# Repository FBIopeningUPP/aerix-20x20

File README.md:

# **AERIX**

i wanted to design my own flight controller for fpv racing, so i made aerix. it fits a 20×20 mm stack and runs on an rp2354a with an icm-40609-d gyro.

i went with solder pads for the esc, receiver and vtx to keep the board small. the 8 rgb leds around the corners are there because they look cool af.

## front and back

| front | back |
| :---: | :---: |
|  |  |

## copper layers

<details>
<summary>see each layer up close</summary>

| front copper | inner copper 1 |
| :---: | :---: |
|  |  |

| inner copper 2 | back copper |
| :---: | :---: |
|  |  |

</details>

## files

- [kicad project](hardware/fc-v1/fc-v1.kicad_pro)
- [gerbers and drill files](hardware/production/fc-v1/fc-v1.zip)
- [interactive BOM](hardware/production/fc-v1/ibom.html) (download and open in a browser)

## bill of materials

| ref | part | qty |
| --- | --- | ---: |
| U1 | RP2354A microcontroller | 1 |
| U3 | ICM-40609-D gyro | 1 |
| U4 | W25Q128JVPIQTR flash | 1 |
| U5 | MP9943GQ-Z 5 V regulator | 1 |
| J1 | USB4105-GF-A USB-C port | 1 |
| LED10–LED17 | WS2812B-2020-V6 RGB LEDs | 8 |
| U2 | DPS368 barometer (optional) | 1 |

[full parts list with quantities and supplier links](hardware/production/fc-v1/aerix-bom.csv)

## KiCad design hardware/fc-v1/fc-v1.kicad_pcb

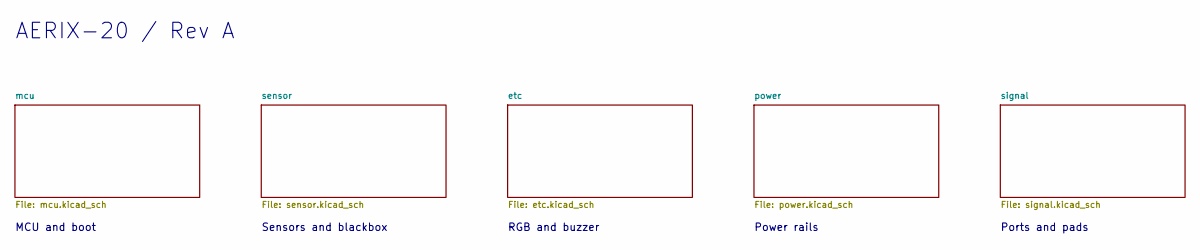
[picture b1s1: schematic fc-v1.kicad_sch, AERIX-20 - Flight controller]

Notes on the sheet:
Ports and pads
Sensors and blackbox
RGB and buzzer
AERIX-20 / Rev A
MCU and boot
Power rails

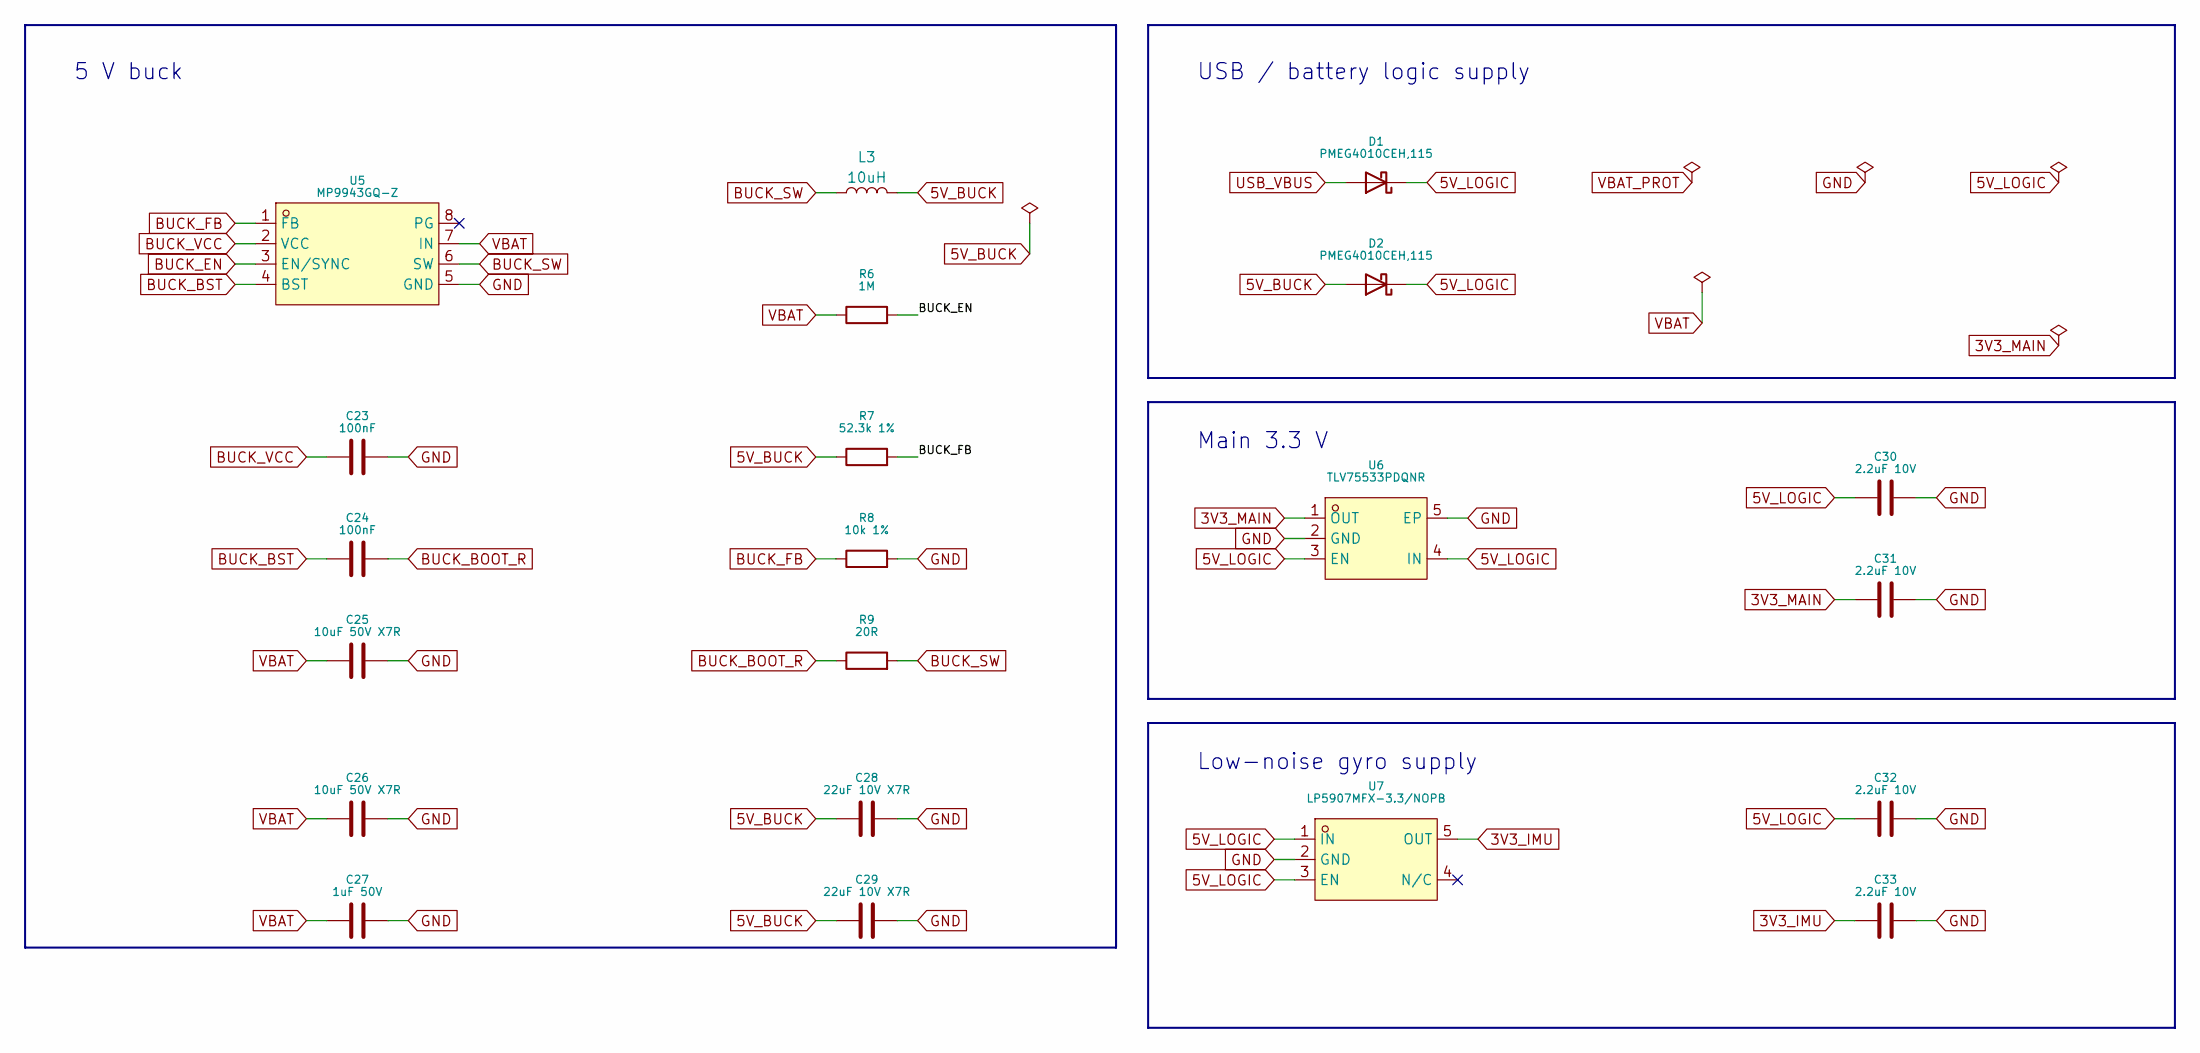
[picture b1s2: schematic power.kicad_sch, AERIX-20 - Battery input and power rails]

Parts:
C23, C24: 100nF; C_0402_1005Metric
C25, C26: 10uF 50V X7R; C_1210_3225Metric
C27: 1uF 50V; C_0603_1608Metric
C28, C29: 22uF 10V X7R; C_0805_2012Metric
C30, C31, C32, C33: 2.2uF 10V; C_0603_1608Metric
D1, D2: PMEG4010CEH,115; D_SOD-123F
L3: 10uH_1.0A_4018; L_APV_ANR4020; Part Number NRS4018T100MDGJ
R6: 1M; R_0402_1005Metric
R7: 52.3k 1%; R_0402_1005Metric
R8: 10k 1%; R_0402_1005Metric
R9: 20R; R_0402_1005Metric
U5: MP9943GQ-Z; QFN-8_L3.0-W3.0-P0.65-BL
U6: TLV75533PDQNR; X2SON-4_L1.0-W1.0-P0.65-TL-EP
U7: LP5907MFX-3.3/NOPB; SOT-23-5_L3.0-W1.7-P0.95-LS2.8-BR

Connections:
3V3_IMU: C33.1, U7.5 (OUT); also elsewhere on the board
3V3_MAIN: C31.1, U6.1 (OUT); also elsewhere on the board
5V_BUCK: C28.1, C29.1, D2.2 (A), L3.2, R7.1; also elsewhere on the board
5V_LOGIC: C30.1, C32.1, D1.1 (K), D2.1 (K), U6.3 (EN), U6.4 (IN), U7.1 (IN), U7.3 (EN)
BUCK_BOOT_R: C24.2, R9.1
BUCK_BST: C24.1, U5.4 (BST)
BUCK_EN: R6.2, U5.3 (EN/SYNC)
BUCK_FB: R7.2, R8.1, U5.1 (FB)
BUCK_SW: L3.1, R9.2, U5.6 (SW)
BUCK_VCC: C23.1, U5.2 (VCC)
GND: C23.2, C25.2, C26.2, C27.2, C28.2, C29.2, C30.2, C31.2, C32.2, C33.2, R8.2, U5.5 (GND), U6.2 (GND), U6.5 (EP), U7.2 (GND); also elsewhere on the board
USB_VBUS: D1.2 (A); also elsewhere on the board
VBAT: C25.1, C26.1, C27.1, R6.1, U5.7 (IN); also elsewhere on the board

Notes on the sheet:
5 V buck
USB / battery logic supply
Main 3.3 V
Low-noise gyro supply

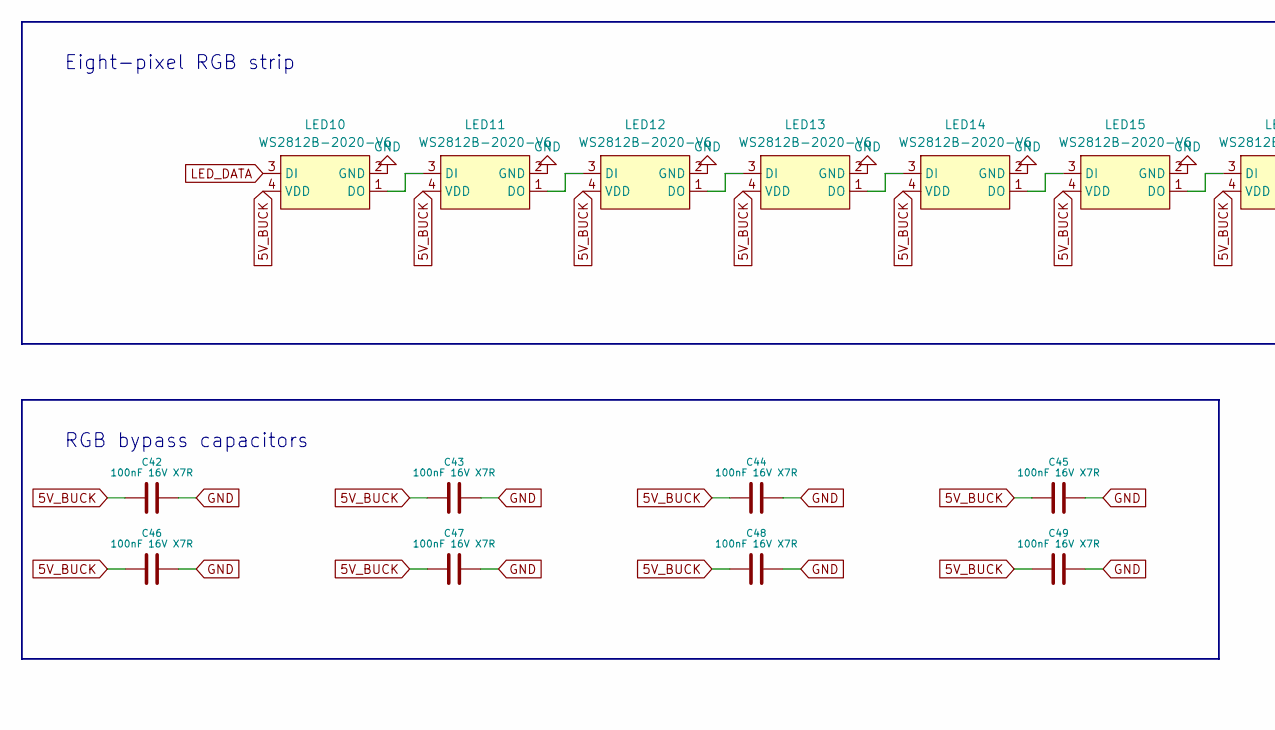
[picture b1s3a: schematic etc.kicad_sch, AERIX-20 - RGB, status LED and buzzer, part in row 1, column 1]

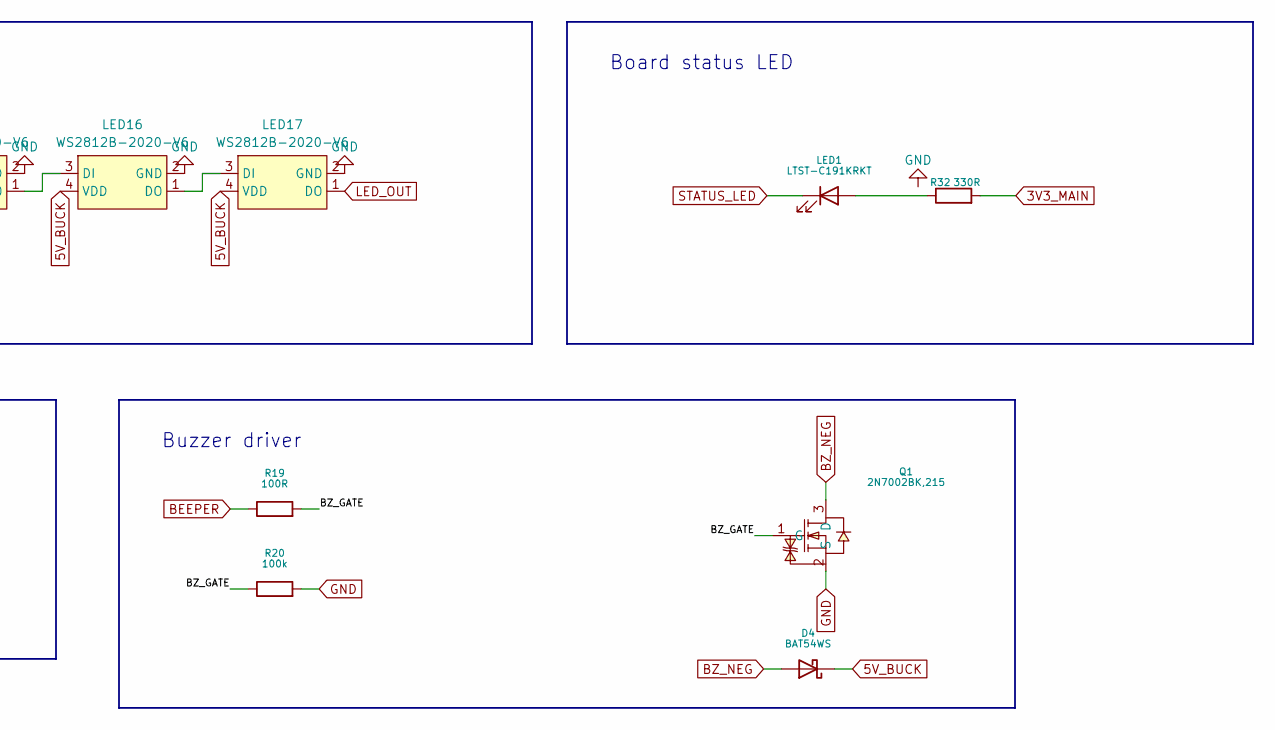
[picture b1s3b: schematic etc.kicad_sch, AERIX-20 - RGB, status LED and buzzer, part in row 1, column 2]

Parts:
C42, C43, C44, C45, C46, C47, C48, C49: 100nF 16V X7R; C_0402_1005Metric
D4: BAT54WS; D_SOD-323
LED1: LTST-C191KRKT; LED_0603_1608Metric
LED10, LED11, LED12, LED13, LED14, LED15, LED16, LED17: WS2812B-2020-V6; LED-SMD_4P-L2.2-W2.0-P1.00_WS2815C-2020-4P; MPN WS2812B-2020-V6; LCSC Part C52917434
Q1: 2N7002BK,215; SOT-23-3_L3.0-W1.7-P0.95-LS2.9-BR
R19: 100R; R_0402_1005Metric
R20: 100k; R_0402_1005Metric
R32: 330R; R_0402_1005Metric

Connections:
3V3_MAIN: R32.2; also elsewhere on the board
5V_BUCK: C42.1, C43.1, C44.1, C45.1, C46.1, C47.1, C48.1, C49.1, D4.1 (K), LED10.4 (VDD), LED11.4 (VDD), LED12.4 (VDD), LED13.4 (VDD), LED14.4 (VDD), LED15.4 (VDD), LED16.4 (VDD), LED17.4 (VDD); also elsewhere on the board
/etc/BZ_GATE: Q1.1 (G), R19.2, R20.1
BEEPER: R19.1; also elsewhere on the board
BZ_NEG: D4.2 (A), Q1.3 (D); also elsewhere on the board
GND: C42.2, C43.2, C44.2, C45.2, C46.2, C47.2, C48.2, C49.2, LED10.2 (GND), LED11.2 (GND), LED12.2 (GND), LED13.2 (GND), LED14.2 (GND), LED15.2 (GND), LED16.2 (GND), LED17.2 (GND), Q1.2 (S), R20.2; also elsewhere on the board
LED_DATA: LED10.3 (DI); also elsewhere on the board
LED_OUT: LED17.1 (DO); also elsewhere on the board
unnamed: LED1.2 (A), R32.1
unnamed: LED10.1 (DO), LED11.3 (DI)
unnamed: LED11.1 (DO), LED12.3 (DI)
unnamed: LED12.1 (DO), LED13.3 (DI)
unnamed: LED13.1 (DO), LED14.3 (DI)
unnamed: LED14.1 (DO), LED15.3 (DI)
unnamed: LED15.1 (DO), LED16.3 (DI)
unnamed: LED16.1 (DO), LED17.3 (DI)
STATUS_LED: LED1.1 (K); also elsewhere on the board

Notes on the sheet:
RGB bypass capacitors
Eight-pixel RGB strip
Board status LED
Buzzer driver

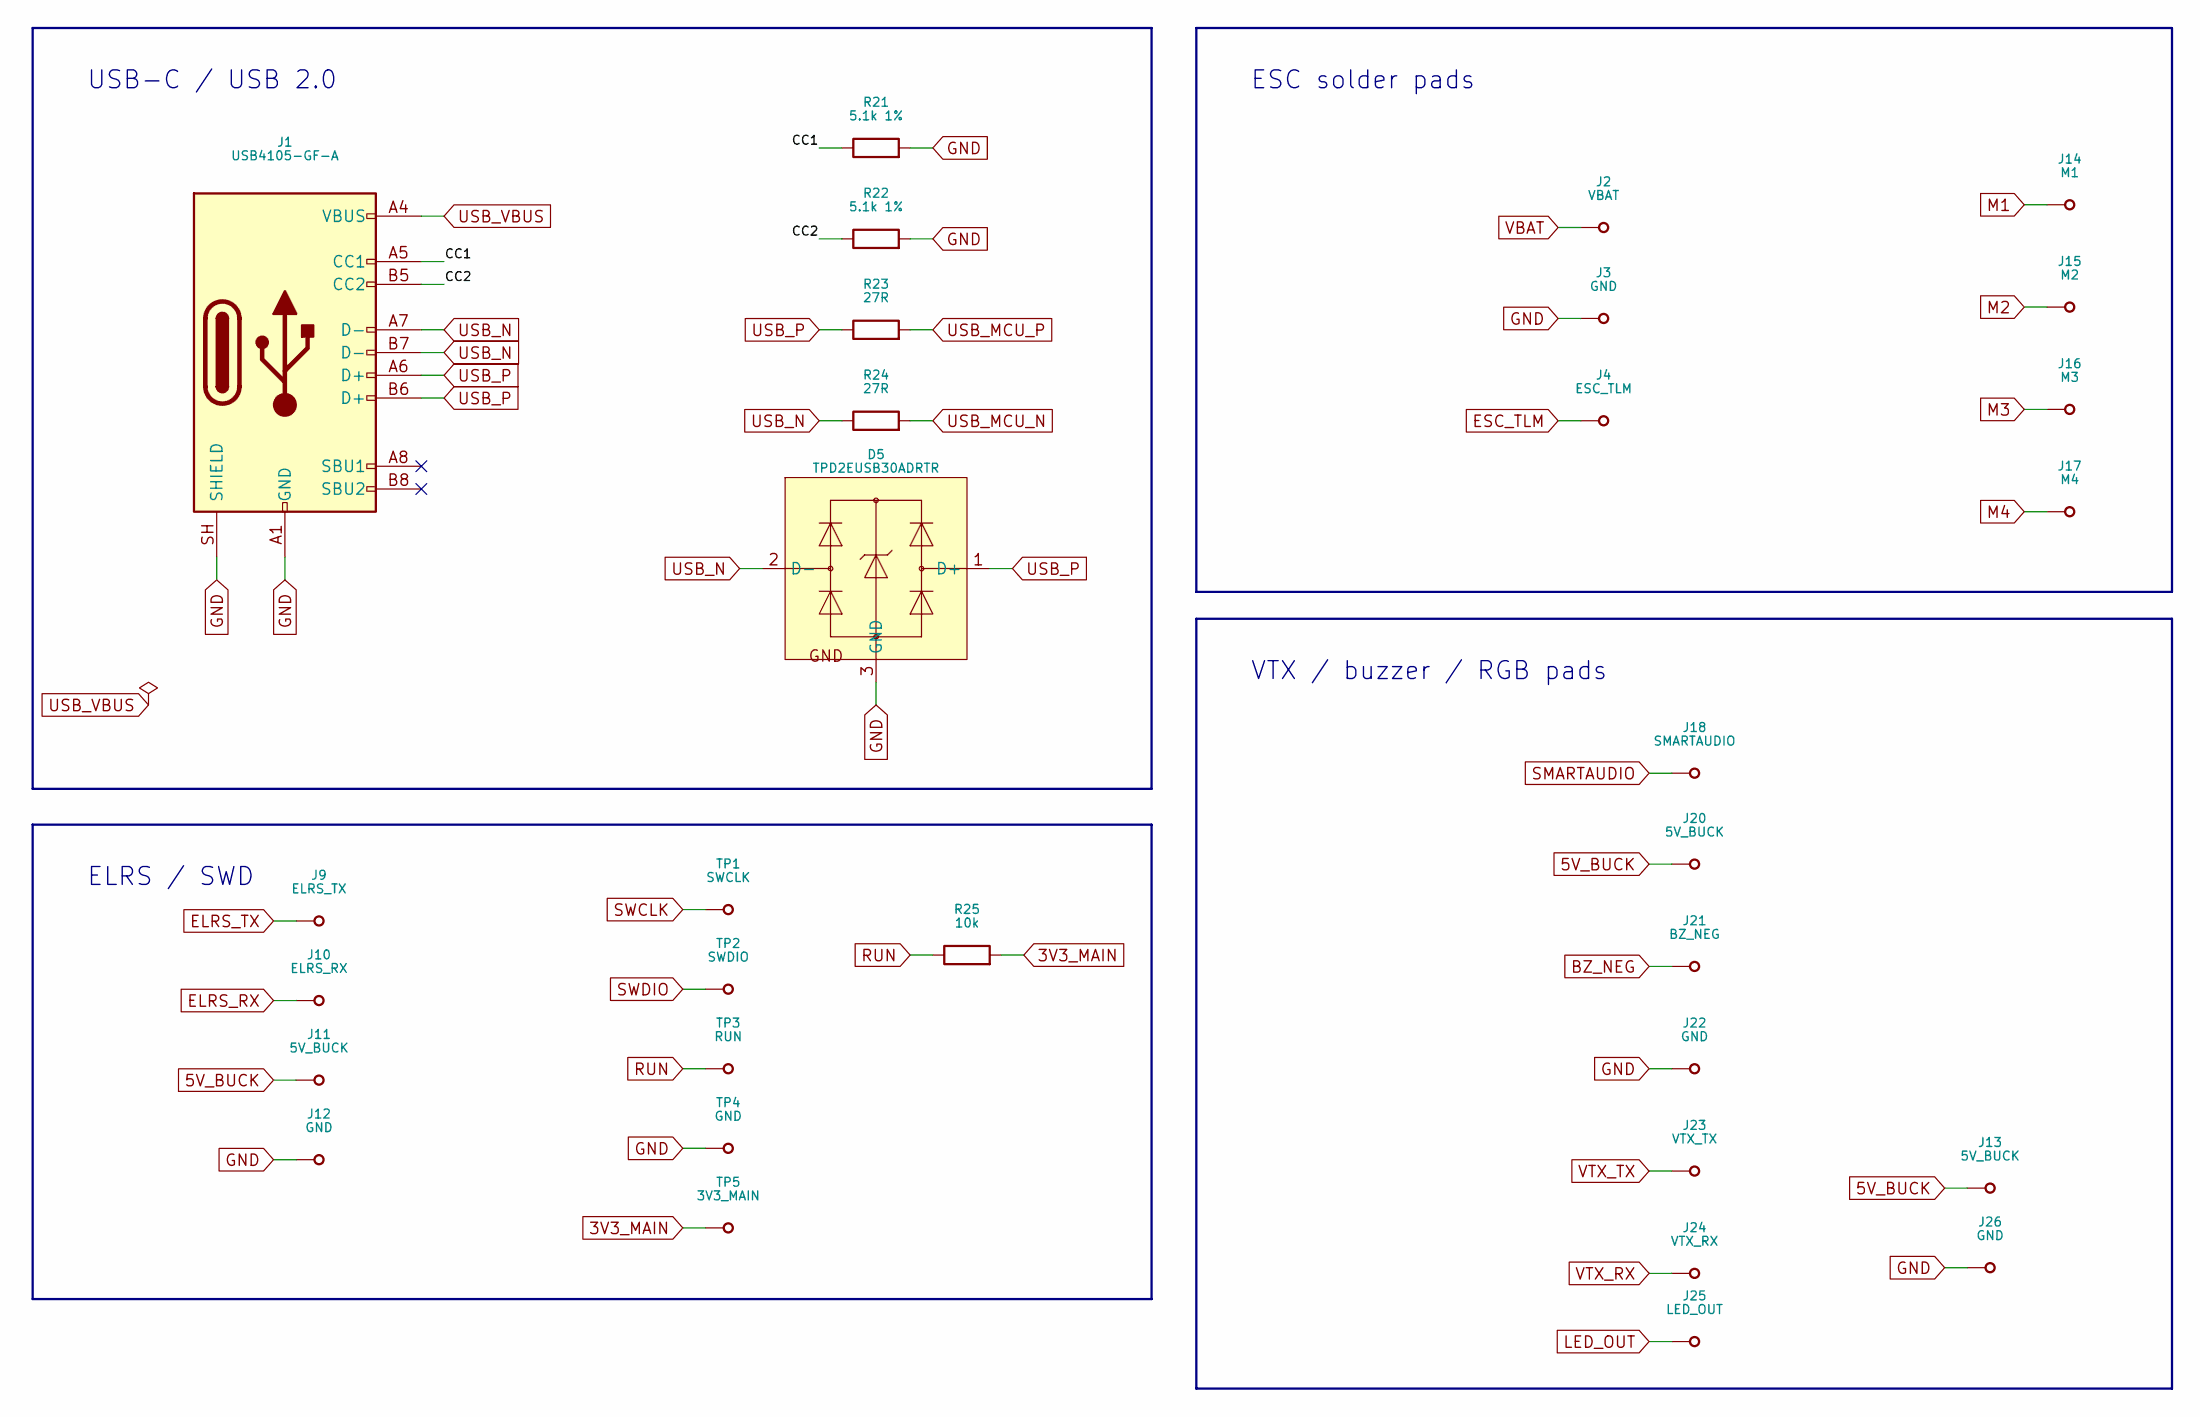
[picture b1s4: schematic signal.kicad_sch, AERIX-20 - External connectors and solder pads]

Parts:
D5: TPD2EUSB30ADRTR; SOT-9X3-3_L1.0-W0.8-P0.35-LS1.0-BR
J1: USB4105-GF-A; USB_C_Receptacle_GCT_USB4105-xx-A_16P_TopMnt_Horizontal
J2: VBAT; WirePad_2.0x2.5mm
J3: GND; WirePad_2.0x2.5mm
J4: ESC_TLM; WirePad_1.5x2.0mm
J9: ELRS_TX; WirePad_1.5x2.0mm
J10: ELRS_RX; WirePad_1.5x2.0mm
J11, J13, J20: 5V_BUCK; WirePad_1.5x2.0mm
J12, J22, J26: GND; WirePad_1.5x2.0mm
J14: M1; WirePad_1.5x2.0mm
J15: M2; WirePad_1.5x2.0mm
J16: M3; WirePad_1.5x2.0mm
J17: M4; WirePad_1.5x2.0mm
J18: SMARTAUDIO; WirePad_1.5x2.0mm
J21: BZ_NEG; WirePad_1.5x2.0mm
J23: VTX_TX; WirePad_1.5x2.0mm
J24: VTX_RX; WirePad_1.5x2.0mm
J25: LED_OUT; WirePad_1.5x2.0mm
R21, R22: 5.1k 1%; R_0402_1005Metric
R23, R24: 27R; R_0402_1005Metric
R25: 10k; R_0402_1005Metric
TP1: SWCLK; ProbePad_D1.0mm
TP2: SWDIO; ProbePad_D1.0mm
TP3: RUN; ProbePad_D1.0mm
TP4: GND; ProbePad_D1.0mm
TP5: 3V3_MAIN; ProbePad_D1.0mm

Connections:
3V3_MAIN: R25.2, TP5.1 (~_1); also elsewhere on the board
5V_BUCK: J11.1 (~_1), J13.1 (~_1), J20.1 (~_1); also elsewhere on the board
/signal/CC1: J1.A5 (CC1), R21.1
/signal/CC2: J1.B5 (CC2), R22.1
BZ_NEG: J21.1 (~_1); also elsewhere on the board
ELRS_RX: J10.1 (~_1); also elsewhere on the board
ELRS_TX: J9.1 (~_1); also elsewhere on the board
ESC_TLM: J4.1 (~_1); also elsewhere on the board
GND: D5.3 (GND), J1.A1 (GND), J1.A12 (GND), J1.B1 (GND), J1.B12 (GND), J1.SH (SHIELD), J3.1 (~_1), J12.1 (~_1), J22.1 (~_1), J26.1 (~_1), R21.2, R22.2, TP4.1 (~_1); also elsewhere on the board
LED_OUT: J25.1 (~_1); also elsewhere on the board
M1: J14.1 (~_1); also elsewhere on the board
M2: J15.1 (~_1); also elsewhere on the board
M3: J16.1 (~_1); also elsewhere on the board
M4: J17.1 (~_1); also elsewhere on the board
RUN: R25.1, TP3.1 (~_1); also elsewhere on the board
SMARTAUDIO: J18.1 (~_1); also elsewhere on the board
SWCLK: TP1.1 (~_1); also elsewhere on the board
SWDIO: TP2.1 (~_1); also elsewhere on the board
USB_MCU_N: R24.2; also elsewhere on the board
USB_MCU_P: R23.2; also elsewhere on the board
USB_N: D5.2 (D-), J1.A7 (D-), J1.B7 (D-), R24.1
USB_P: D5.1 (D+), J1.A6 (D+), J1.B6 (D+), R23.1
USB_VBUS: J1.A4 (VBUS), J1.A9 (VBUS), J1.B4 (VBUS), J1.B9 (VBUS); also elsewhere on the board
VBAT: J2.1 (~_1); also elsewhere on the board
VTX_RX: J24.1 (~_1); also elsewhere on the board
VTX_TX: J23.1 (~_1); also elsewhere on the board

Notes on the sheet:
VTX / buzzer / RGB pads
ESC solder pads
USB-C / USB 2.0
ELRS / SWD

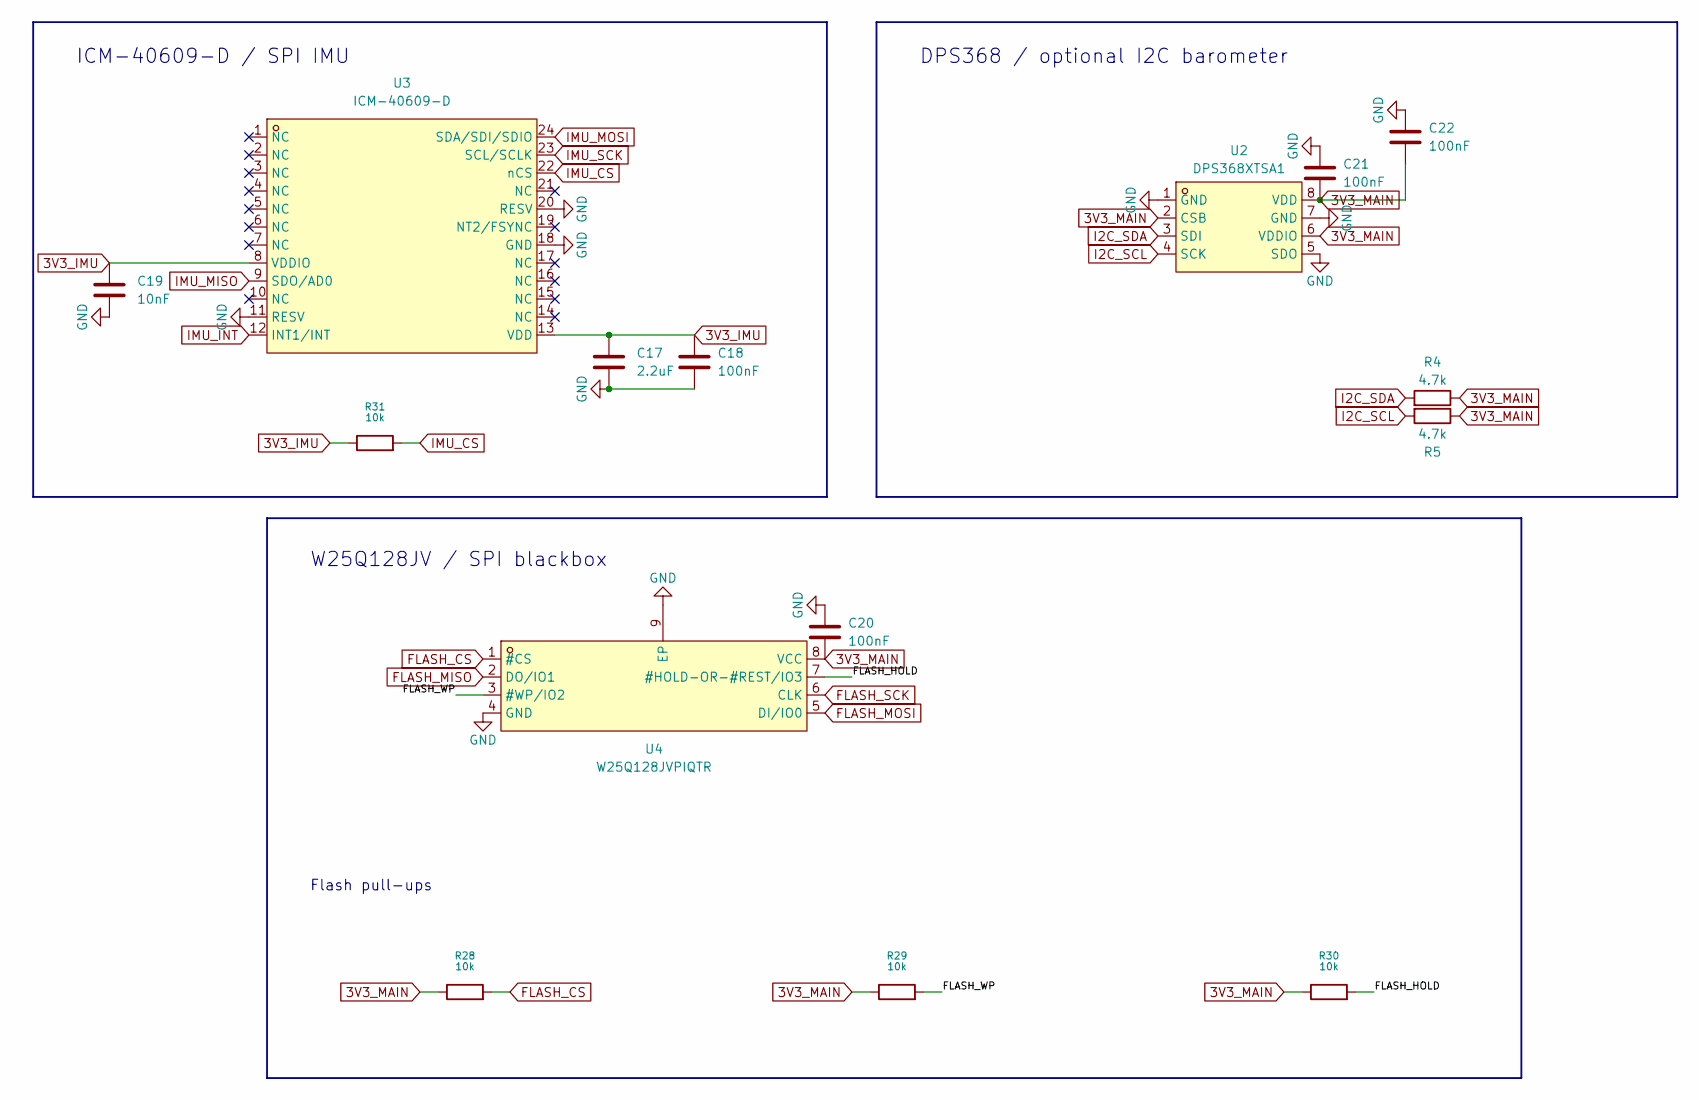
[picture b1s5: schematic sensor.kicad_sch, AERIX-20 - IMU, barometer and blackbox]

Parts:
C17: 2.2uF; C_0603_1608Metric
C18, C20, C21, C22: 100nF; C_0402_1005Metric
C19: 10nF; C_0402_1005Metric
R4, R5: 4.7k; R_0402_1005Metric
R28, R29, R30, R31: 10k; R_0402_1005Metric
U2: DPS368XTSA1; LGA-8_L2.5-W2.0-P0.65-TR_DPS368; MPN DPS368XTSA1; LCSC Part C3232508
U3: ICM-40609-D; LGA-24_L3.0-W3.0-P0.40-TL; MPN ICM-40609-D; LCSC Part C5360621
U4: W25Q128JVPIQTR; WSON-8_L6.0-W5.0-P1.27-BL-EP; MPN W25Q128JVPIQ; LCSC Part C190862

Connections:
3V3_IMU: C17.1, C18.1, C19.1, R31.1, U3.8 (VDDIO), U3.13 (VDD); also elsewhere on the board
3V3_MAIN: C20.2, C21.2, C22.2, R4.2, R5.2, R28.1, R29.1, R30.1, U2.2 (CSB), U2.6 (VDDIO), U2.8 (VDD), U4.8 (VCC); also elsewhere on the board
/sensor/FLASH_HOLD: R30.2, U4.7 (#HOLD-OR-#REST/IO3)
/sensor/FLASH_WP: R29.2, U4.3 (#WP/IO2)
FLASH_CS: R28.2, U4.1 (#CS); also elsewhere on the board
FLASH_MISO: U4.2 (DO/IO1); also elsewhere on the board
FLASH_MOSI: U4.5 (DI/IO0); also elsewhere on the board
FLASH_SCK: U4.6 (CLK); also elsewhere on the board
GND: C17.2, C18.2, C19.2, C20.1, C21.1, C22.1, U2.1 (GND), U2.5 (SDO), U2.7 (GND), U3.11 (RESV), U3.18 (GND), U3.20 (RESV), U4.4 (GND), U4.9 (EP); also elsewhere on the board
I2C_SCL: R5.1, U2.4 (SCK); also elsewhere on the board
I2C_SDA: R4.1, U2.3 (SDI); also elsewhere on the board
IMU_CS: R31.2, U3.22 (nCS); also elsewhere on the board
IMU_INT: U3.12 (INT1/INT); also elsewhere on the board
IMU_MISO: U3.9 (SDO/AD0); also elsewhere on the board
IMU_MOSI: U3.24 (SDA/SDI/SDIO); also elsewhere on the board
IMU_SCK: U3.23 (SCL/SCLK); also elsewhere on the board

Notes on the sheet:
ICM-40609-D / SPI IMU
DPS368 / optional I2C barometer
Flash pull-ups
W25Q128JV / SPI blackbox

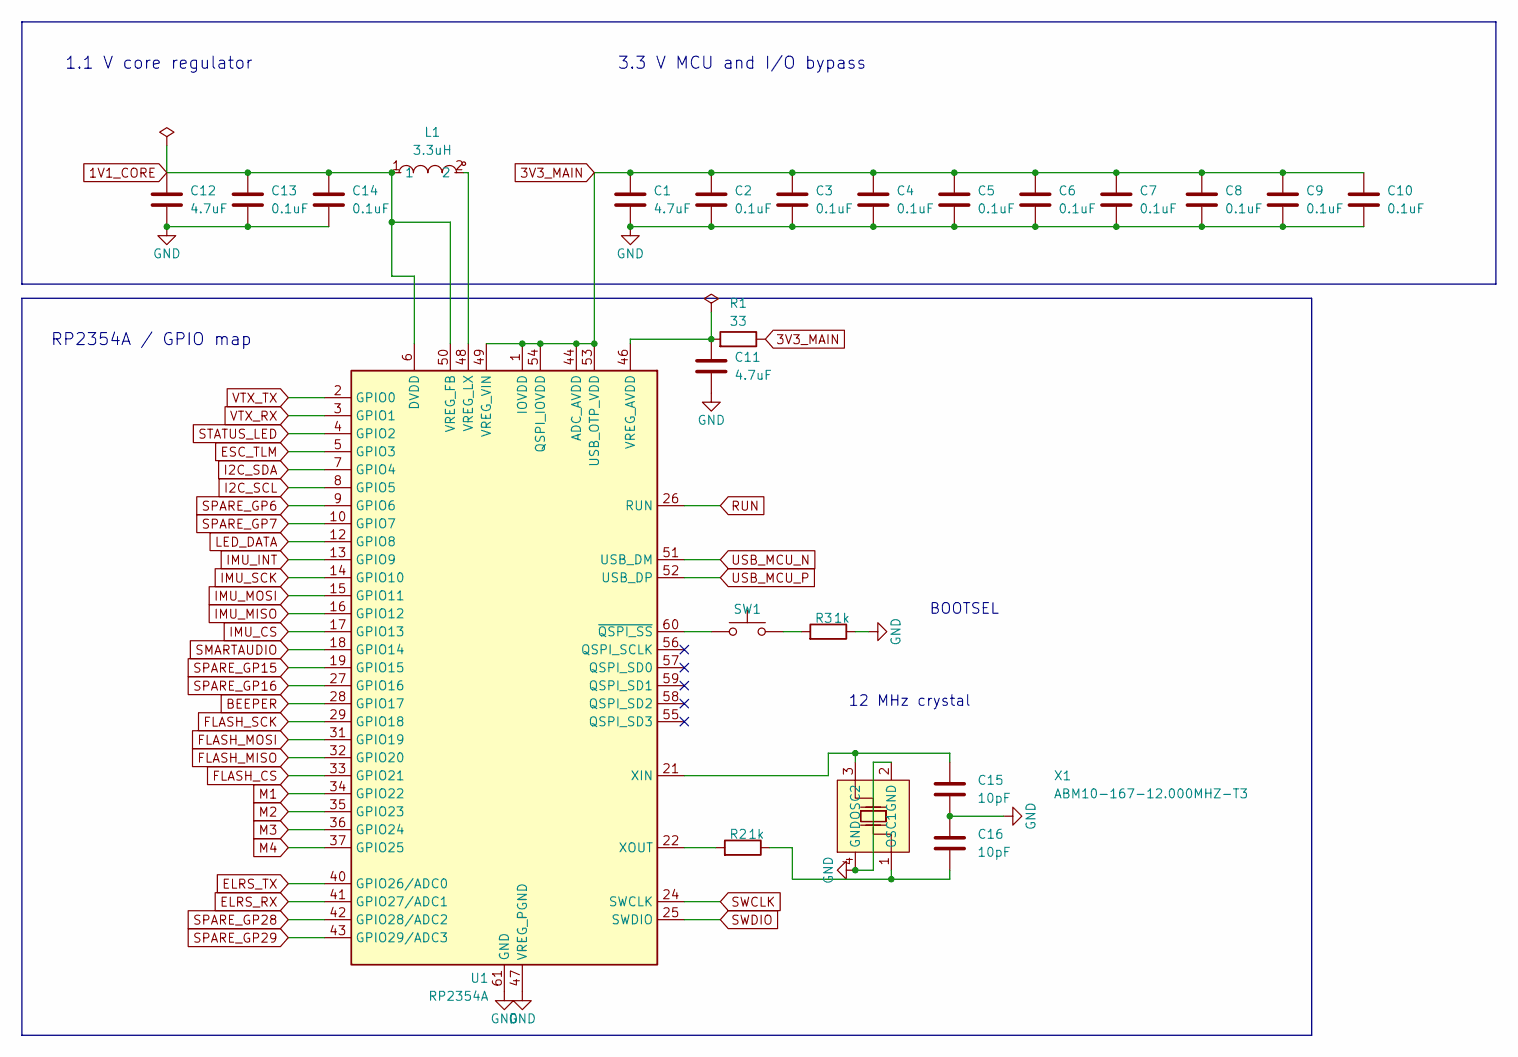
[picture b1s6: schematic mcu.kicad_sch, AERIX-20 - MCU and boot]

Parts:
C1, C11, C12: 4.7uF; C_0402_1005Metric
C2, C3, C4, C5, C6, C7, C8, C9, C10, C13, C14: 0.1uF; C_0402_1005Metric
C15, C16: 10pF; C_0402_1005Metric
L1: 3.3uH; IND-SMD_L2.0-W1.6_AOTA-B201610S3R3-101-T; MPN AOTA-B201610S3R3-101-T; LCSC Part C42411119
R1: 33; R_0402_1005Metric
R2, R3: 1k; R_0402_1005Metric
SW1: Momentary Tactile Button - Biege; Push_SMD_4.2x3.2mm_h2.5mm_Beige
U1: RP2354A; QFN-60-1EP_7x7mm_P0.4mm_EP3.4x3.4mm
X1: ABM10-167-12.000MHZ-T3; CRYSTAL-SMD_4P-L2.5-W2.0-BL; MPN ABM10-167-12.000MHZ-T3; LCSC Part C1985295

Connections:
1V1_CORE: C12.1, C13.1, C14.1, L1.1, U1.6 (DVDD), U1.23 (DVDD), U1.39 (DVDD), U1.50 (VREG_FB)
3V3_MAIN: C1.1, C2.1, C3.1, C4.1, C5.1, C6.1, C7.1, C8.1, C9.1, C10.1, R1.2, U1.1 (IOVDD), U1.11 (IOVDD), U1.20 (IOVDD), U1.30 (IOVDD), U1.38 (IOVDD), U1.44 (ADC_AVDD), U1.45 (IOVDD), U1.49 (VREG_VIN), U1.53 (USB_OTP_VDD), U1.54 (QSPI_IOVDD); also elsewhere on the board
BEEPER: U1.28 (GPIO17); also elsewhere on the board
ELRS_RX: U1.41 (GPIO27/ADC1); also elsewhere on the board
ELRS_TX: U1.40 (GPIO26/ADC0); also elsewhere on the board
ESC_TLM: U1.5 (GPIO3); also elsewhere on the board
FLASH_CS: U1.33 (GPIO21); also elsewhere on the board
FLASH_MISO: U1.32 (GPIO20); also elsewhere on the board
FLASH_MOSI: U1.31 (GPIO19); also elsewhere on the board
FLASH_SCK: U1.29 (GPIO18); also elsewhere on the board
GND: C1.2, C2.2, C3.2, C4.2, C5.2, C6.2, C7.2, C8.2, C9.2, C10.2, C11.2, C12.2, C13.2, C14.2, C15.2, C16.1, R3.2, U1.47 (VREG_PGND), U1.61 (GND), X1.2 (GND), X1.4 (GND); also elsewhere on the board
I2C_SCL: U1.8 (GPIO5); also elsewhere on the board
I2C_SDA: U1.7 (GPIO4); also elsewhere on the board
IMU_CS: U1.17 (GPIO13); also elsewhere on the board
IMU_INT: U1.13 (GPIO9); also elsewhere on the board
IMU_MISO: U1.16 (GPIO12); also elsewhere on the board
IMU_MOSI: U1.15 (GPIO11); also elsewhere on the board
IMU_SCK: U1.14 (GPIO10); also elsewhere on the board
LED_DATA: U1.12 (GPIO8); also elsewhere on the board
M1: U1.34 (GPIO22); also elsewhere on the board
M2: U1.35 (GPIO23); also elsewhere on the board
M3: U1.36 (GPIO24); also elsewhere on the board
M4: U1.37 (GPIO25); also elsewhere on the board
unnamed: R3.1, SW1.2
unnamed: C11.1, R1.1, U1.46 (VREG_AVDD)
unnamed: L1.2, U1.48 (VREG_LX)
unnamed: C15.1, U1.21 (XIN), X1.3 (OSC2)
unnamed: R2.1, U1.22 (XOUT)
unnamed: SW1.1, U1.60 (~QSPI_SS)
unnamed: C16.2, R2.2, X1.1 (OSC1)
RUN: U1.26 (RUN); also elsewhere on the board
SMARTAUDIO: U1.18 (GPIO14); also elsewhere on the board
SPARE_GP6: U1.9 (GPIO6)
SPARE_GP7: U1.10 (GPIO7)
SPARE_GP15: U1.19 (GPIO15)
SPARE_GP16: U1.27 (GPIO16)
SPARE_GP28: U1.42 (GPIO28/ADC2)
SPARE_GP29: U1.43 (GPIO29/ADC3)
STATUS_LED: U1.4 (GPIO2); also elsewhere on the board
SWCLK: U1.24 (SWCLK); also elsewhere on the board
SWDIO: U1.25 (SWDIO); also elsewhere on the board
USB_MCU_N: U1.51 (USB_DM); also elsewhere on the board
USB_MCU_P: U1.52 (USB_DP); also elsewhere on the board
VTX_RX: U1.3 (GPIO1); also elsewhere on the board
VTX_TX: U1.2 (GPIO0); also elsewhere on the board

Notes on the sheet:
1.1 V core regulator
12 MHz crystal
RP2354A / GPIO map
BOOTSEL
3.3 V MCU and I/O bypass

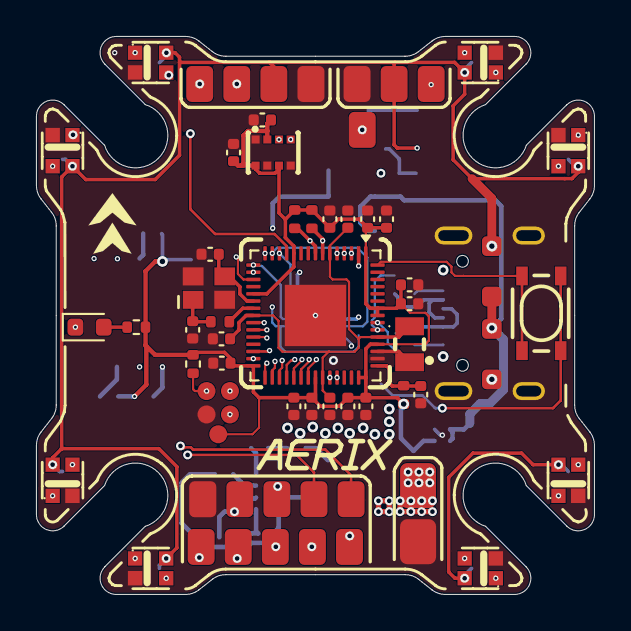
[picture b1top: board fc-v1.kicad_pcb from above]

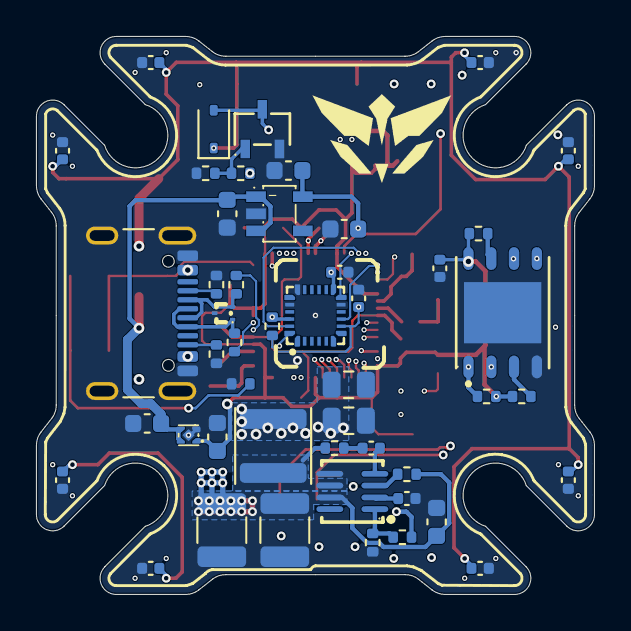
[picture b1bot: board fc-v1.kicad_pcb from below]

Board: 4 copper layers, 31.0 x 31.0 mm, 113 parts (48 on the bottom side), 67 nets.

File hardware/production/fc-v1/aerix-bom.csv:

Part,Quantity,References,Footprint,LCSC Part #,Supplier link,Notes
"Capacitor, 4.7uF",3,"C1, C11, C12",0402,,https://www.digikey.in/en/products/result?keywords=Capacitor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,
"Capacitor, 0.1uF",11,"C10, C13, C14, C2, C3, C4, C5, C6, C7, C8, C9",0402,,https://www.digikey.in/en/products/result?keywords=Capacitor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,
"Capacitor, 10pF",2,"C15, C16",0402,,https://www.digikey.in/en/products/result?keywords=Capacitor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,
"Capacitor, 2.2uF",1,C17,0603,,https://www.digikey.in/en/products/result?keywords=Capacitor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,
"Capacitor, 100nF",6,"C18, C20, C21, C22, C23, C24",0402,,https://www.digikey.in/en/products/result?keywords=Capacitor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,
"Capacitor, 10nF",1,C19,0402,,https://www.digikey.in/en/products/result?keywords=Capacitor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,
"Capacitor, 10uF 50V X7R",2,"C25, C26",1210,,https://www.digikey.in/en/products/result?keywords=Capacitor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,
"Capacitor, 1uF 50V",1,C27,0603,,https://www.digikey.in/en/products/result?keywords=Capacitor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,
"Capacitor, 22uF 10V X7R",2,"C28, C29",0805,,https://www.digikey.in/en/products/result?keywords=Capacitor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,
"Capacitor, 2.2uF 10V",4,"C30, C31, C32, C33",0603,,https://www.digikey.in/en/products/result?keywords=Capacitor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,
"Capacitor, 100nF 16V X7R",8,"C42, C43, C44, C45, C46, C47, C48, C49",0402,,https://www.digikey.in/en/products/result?keywords=Capacitor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,
"PMEG4010CEH,115",2,"D1, D2",D_SOD-123F,,https://www.digikey.in/en/products/result?keywords=PMEG4010C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,
BAT54WS,1,D4,D_SOD-323,,https://www.digikey.in/en/products/result?keywords=BAT54WS,
TPD2EUSB30ADRTR,1,D5,SOT-9X3-3_L1.0-W0.8-P0.35-LS1.0-BR,C94934,https://www.lcsc.com/product-detail/C94934.html,
USB4105-GF-A,1,J1,USB_C_Receptacle_GCT_USB4105-xx-A_16P_TopMnt_Horizontal,,https://www.digikey.in/en/products/result?keywords=USB4105-GF-A,
3.3 uH inductor (AOTA-B201610S3R3-101-T),1,L1,IND-SMD_L2.0-W1.6_AOTA-B201610S3R3-101-T,C42411119,https://www.lcsc.com/product-detail/C42411119.html,
"10 uH, 1 A inductor (4 x 4 x 1.8 mm)",1,L3,L_APV_ANR4020,,https://www.digikey.in/en/products/result?keywords=10%20uH%2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,
LTST-C191KRKT,1,LED1,0603,,https://www.digikey.in/en/products/result?keywords=LTST-C191KRKT,
WS2812B-2020-V6,8,"LED10, LED11, LED12, LED13, LED14, LED15, LED16, LED17",LED-SMD_4P-L2.2-W2.0-P1.00_WS2815C-2020-4P,C52917434,https://www.lcsc.com/product-detail/C52917434.html,
"2N7002BK,215",1,Q1,SOT-23-3_L3.0-W1.7-P0.95-LS2.9-BR,C282405,https://www.lcsc.com/product-detail/C282405.html,
"Resistor, 33 ohm",1,R1,0402,,https://www.digikey.in/en/products/result?keywords=Resistor%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,
"Resistor, 100R",1,R19,0402,,https://www.digikey.in/en/products/result?keywords=Resistor%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,
"Resistor, 1k",2,"R2, R3",0402,,https://www.digikey.in/en/products/result?keywords=Resistor%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,
"Resistor, 100k",1,R20,0402,,https://www.digikey.in/en/products/result?keywords=Resistor%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,
"Resistor, 5.1k 1%",2,"R21, R22",0402,,https://www.digikey.in/en/products/result?keywords=Resistor%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,
"Resistor, 27R",2,"R23, R24",0402,,https://www.digikey.in/en/products/result?keywords=Resistor%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,
"Resistor, 10k",5,"R25, R28, R29, R30, R31",0402,,https://www.digikey.in/en/products/result?keywords=Resistor%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,
"Resistor, 330R",1,R32,0402,,https://www.digikey.in/en/products/result?keywords=Resistor%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,
"Resistor, 4.7k",2,"R4, R5",0402,,https://www.digikey.in/en/products/result?keywords=Resistor%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,
"Resistor, 1M",1,R6,0402,,https://www.digikey.in/en/products/result?keywords=Resistor%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,
"Resistor, 52.3k 1%",1,R7,0402,,https://www.digikey.in/en/products/result?keywords=Resistor%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,
"Resistor, 10k 1%",1,R8,0402,,https://www.digikey.in/en/products/result?keywords=Resistor%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,
"Resistor, 20R",1,R9,0402,,https://www.digikey.in/en/products/result?keywords=Resistor%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,
Momentary SMD push button (4.2 x 3.2 x 2.5 mm),1,SW1,Push_SMD_4.2x3.2mm_h2.5mm_Beige,,https://www.digikey.in/en/products/result?keywords=Momentary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,
RP2354A,1,U1,QFN-60-1EP_7x7mm_P0.4mm_EP3.4x3.4mm,,https://www.digikey.in/en/products/result?keywords=RP2354A,
DPS368XTSA1,1,U2,LGA-8_L2.5-W2.0-P0.65-TR_DPS368,C3232508,https://www.lcsc.com/product-detail/C3232508.html,Optional barometer
ICM-40609-D,1,U3,LGA-24_L3.0-W3.0-P0.40-TL,C5360621,https://www.lcsc.com/product-detail/C5360621.html,
W25Q128JVPIQTR,1,U4,WSON-8_L6.0-W5.0-P1.27-BL-EP,C190862,https://www.lcsc.com/product-detail/C190862.html,
MP9943GQ-Z,1,U5,QFN-8_L3.0-W3.0-P0.65-BL,C477821,https://www.lcsc.com/product-detail/C477821.html,
TLV75533PDQNR,1,U6,X2SON-4_L1.0-W1.0-P0.65-TL-EP,C2861882,https://www.lcsc.com/product-detail/C2861882.html,
LP5907MFX-3.3/NOPB,1,U7,SOT-23-5_L3.0-W1.7-P0.95-LS2.8-BR,C80670,https://www.lcsc.com/product-detail/C80670.html,
ABM10-167-12.000MHZ-T3,1,X1,CRYSTAL-SMD_4P-L2.5-W2.0-BL,C1985295,https://www.lcsc.com/product-detail/C1985295.html,
